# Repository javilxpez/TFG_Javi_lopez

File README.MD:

El ESP32 tiene periféricos UART de silicio dedicados. Cuando el servo responde por RS485, el hardware UART recibe los bytes en su propia FIFO con interrupciones, sin tocar el CPU. Cuando ModbusMaster llama a readBytes(), los bytes ya están esperando en el buffer — la espera es prácticamente cero (~1-3ms total por operación).

CPU: enviamos frame → hacemos otra cosa → bytes ya están → leemos y seguimos
                       ↑ hardware lo hace solo
Raspberry Pi Pico 2: UART por PIO (SerialPIO)

El Pico no tiene pines UART en GP13/GP14 (los pines que necesitamos). Por eso usamos SerialPIO — una máquina de estado programable (PIO) que emula el UART en software.

El problema es que SerialPIO hace el polling de otra manera, y parece que el setTimeout(20) no funciona igual que en un UART hardware. Lo que ocurría en la práctica:

Core0: enviamos frame → esperamos respuesta → TIMEOUT (20ms o más) → seguimos
                          ↑ esto bloqueaba todo el Core0
Diez writes × 20ms = 200ms bloqueado. Más las lecturas de monitorización. Todo acumulado daba los 3-4 segundos.

Por qué el timeout no funcionaba

ModbusMaster tiene su propio bucle interno esperando respuesta:

while (millis() - start < timeout) {
    if (_serial->available()) { // lee bytes }
}
En ESP32, available() devuelve true casi inmediatamente (hardware). En SerialPIO, el PIO puede tener más latencia en reportar bytes listos, o el timeout interno no se aplicaba correctamente.

Por qué el dual-core lo soluciona

No cambia nada del comportamiento de SerialPIO. Lo que cambia es que ahora ese bloqueo ocurre en Core1, que no tiene nada más que hacer. Core0 corre libre sin esperar nunca.

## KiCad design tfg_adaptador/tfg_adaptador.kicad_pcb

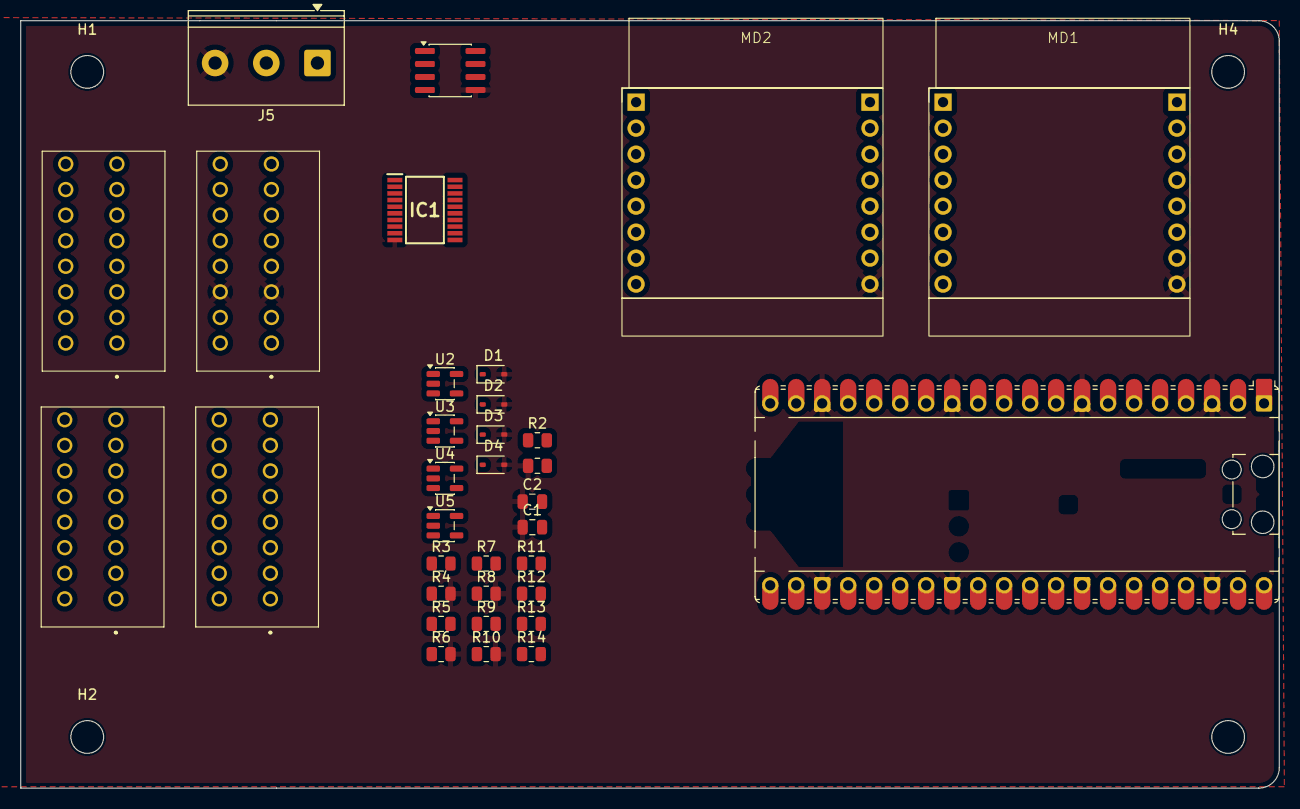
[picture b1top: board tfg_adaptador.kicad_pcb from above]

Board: 2 copper layers, 123.0 x 75.0 mm, 38 parts (0 on the bottom side), 30 nets, no tracks yet.

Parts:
A1: RaspberryPi_Pico; RaspberryPi_Pico_Common_Unspecified
C1, C2: 100nf; C_0805_2012Metric
D1, D2, D3, D4: BZX384xxxx; D_SOD-323
H1, H2, H3, H4: MountingHole; MountingHole_3.2mm_M3
IC1: TPS4H000AQPWPRQ1; SOP65P640X120-20N
J1, J2, J3, J4: Screw_Terminal_01x08; terminal02x08
J5: Screw_Terminal_01x03; TerminalBlock_Phoenix_PT-1,5-3-5.0-H_1x03_P5.00mm_Horizontal
MD1, MD2: MicroBus_S
R1, R2: 10K; R_0805_2012Metric
R3, R5, R7, R9: 1.7 K; R_0805_2012Metric
R4, R6, R8, R10: 3.3 K; R_0805_2012Metric
R11, R12, R13, R14: 1K; R_0805_2012Metric
U1: THVD1400D; SOIC-8_3.9x4.9mm_P1.27mm
U2, U3, U4, U5: MCP6001-OT; SOT-23-5

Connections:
+3.3V: A1.17 (GPIO13), A1.36 (3V3), C1.2, C2.2, MD1.7 (+3.3V), MD2.7 (+3.3V), R2.1, R2.2, U1.1 (RO), U1.8 (VCC)
+5V: A1.40 (VBUS), IC1.17 (VS_1)
/AOUT1: A1.21 (GPIO16), R3.2, R4.1
/AOUT2: A1.22 (GPIO17), R5.2, R6.1
/AOUT3: A1.24 (GPIO18), R7.2, R8.1
/AOUT4: A1.25 (GPIO19), R9.2, R10.1
/DOUT1: A1.6 (GPIO4), D1.1 (K), R11.2
/DOUT2: A1.7 (GPIO5), D2.1 (K), R12.2
/DOUT3: A1.9 (GPIO6), D3.1 (K), R13.2
/DOUT4: A1.10 (GPIO7), D4.1 (K), R14.2
/SCL1: A1.2 (GPIO1), MD1.13 (SCL)
/SCL2: A1.5 (GPIO3), MD2.13 (SCL)
/SDA1: A1.1 (GPIO0), MD1.14 (SDA)
/SDA2: A1.4 (GPIO2), MD2.14 (SDA)
/SIN1: A1.11 (GPIO8), IC1.1 (IN1)
/SIN2: A1.12 (GPIO9), IC1.2 (IN2)
/SIN3: A1.14 (GPIO10), IC1.3 (IN3)
/SIN4: A1.15 (GPIO11), IC1.4 (IN4)
/SOUT1: IC1.20 (OUT1), J4.8
/SOUT2: IC1.19 (OUT2), J4.7
/SOUT3: IC1.16 (OUT3), J4.6
/SOUT4: IC1.15 (OUT4), J4.5
GND: A1.3 (GND), A1.8 (GND), A1.13 (GND), A1.18 (GND), A1.23 (GND), A1.28 (GND), A1.38 (GND), C1.1, C2.1, D1.2 (A), D2.2 (A), D3.2 (A), D4.2 (A), IC1.10 (GND), J2.3, J5.3, MD1.16 (GND), MD2.16 (GND), R1.1, R4.2, R6.2, R8.2, R10.2, U1.5 (GND)
unnamed: A1.19 (GPIO14), A1.20 (GPIO15), R1.2, U1.2 (~RE), U1.3 (DE), U1.4 (DI)
unnamed: J5.1, U1.6 (A)
unnamed: J5.2, U1.7 (B)
unnamed: R3.1, U2.1, U2.4 (-)
unnamed: R5.1, U3.1, U3.4 (-)
unnamed: R7.1, U4.1, U4.4 (-)
unnamed: R9.1, U5.1, U5.4 (-)

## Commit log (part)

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2026-03-04 Create loadcell_torquemode.py
    V1.0
    Control por celula de carga+ torque mode.
2026-03-04 Create speedtorque_mode.ino
    Primera version de arduino.
    Speed mode+torque mode funcional.
    A falta de implementar el lazo de control con la celula de carga.
2026-03-05 Create monitor.py
    Codigo con interfaz funcional:
    Implementada la comunicacion con el servo y celula de carga.
    Distintos modos de uso modo speed y modo torque.
    VERSION 1.0 pendiente a realizar cambios de optimización
2026-03-05 Create firmware.ino
    Código imolementado en el módulo que recibe el valor de la celula de carga
2026-03-05 Update monitor.py
    code implementation
    v1.1
2026-03-10 code v1.0
    todo el codigo actualizado
2026-03-10 Replaced magic numbers by defines on modbusvars
2026-03-10 updated variables to control structures and updated controller
2026-03-10 Deleted non functional set modes
2026-03-10 Addes braking resistor parameters C10-13
2026-03-10 added all the parameters
2026-03-10 non functional print resolved
2026-03-10 reset parameters added
2026-03-10 added controlling parameters stiffnes level and torque+speed limits in torque mode
2026-03-13 PCB adapter
    Pcb design kicad
2026-03-17 ACTUALIZACION PCB
2026-06-20 V2.0 TEST RASPBERRY ADDED
2026-06-20 somechanges
2026-06-22 COMUNICATION OK NO CONTROL
2026-06-22 no control
2026-06-30 se añade dualcore codigo correctoa falta de maqueta final
